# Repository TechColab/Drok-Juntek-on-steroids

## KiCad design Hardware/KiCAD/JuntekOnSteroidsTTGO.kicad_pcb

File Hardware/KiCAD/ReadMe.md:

# Goal:
-----
THT
No bigger than original board
Economise where possible
Include serial & other connector - just in case.

# SoFar:
------
## Gen.1 - on-board ADC
### 2021-03-17
Board outline is approx 80% of the original
All done first draft.
Options for connection to GNDA, GNDD or both.
Check size of TFT board when over-laid - perfect match for the minimalised outline.
### 2021-03-19
Swap GPIO12 & 15 for easier layout.
Put I2C on the port in place of SWIM as ESP32 doesn't have that.
Route !ON signal with jumpered options.
Move solder-bridges to bottom.
Add axis origin
Save schematic as PDF
### 2021-03-20
Confirm THT not SMT
Add TestPoint for flying-wire to Vin
Add solder bridge option for Vin_sense
Chane I2C pin order
### 2021-03-21
Renamed to correct spelling!
### 2021-05-03
Change pin numbering on I2C to match DFRobot pinout.
Re-route traces for I2C to ease changing to other pinouts.
Move Gerbers to sub-folder for neatness & easier handling.

## Gen.2 - dedicated ADC
### 2021-05-20
I2C connector as a 4-pin adjacent to a 2-pin.
Grove is 2mm not 2.54mm pitch but same pin-out as many others.
Along west edge to use horizontal pin headder, to make case / panel mount easier.
Test-point anchors for flying leads to off-board components.
In the schematic A0-A3 are on the ADC board & ADC0-ADC3 are on the TTGO - so they dont have conflicting names. 
### 2021-08-15
Major re-allocation of pins, noting multi-purpose functions of TTGO device (in only, boot restrictions etc.)
Route analogue signals via solder-bridge switch to both ADC1115 & TTGO to enable option of cheaper rough version.
Add pin for LoadPWM function so TTGO can connect the load by MOSFET and do controlled discharge of a battery.
Separate expansion connector into 2 separate rows for easier positioning & allow SIL only option.
Put external connections, including power, I2C, serial, DAC in a breadboard-friendly row.
Remove extra I2C, serial & power SIL headers as all can be accessed form the expansion SIL.
Set outline based on worst of DKP6012 & B3603, 1 col less on west, 1 row extra on north.
Add a spreadsheet table comparing pinouts of different PSUs & TTGO functions/restrictions.
### 2021-08-17
Remove unwanted resistor, rename a few resistors & two jumpers.
Add a jumper to break AltVinSense from J1.7 for models when CV/CC is on J1.3 & FanPWM is on J1.7
### 2021-08-19
Replace complex series of solder-bridge jumpers with a wire-patch-field.
Replace DIL expansion connector with SIL to free up board space & make easier for end-users.
Move TTGO south a bit for clearance with PSU cap.  Added a couple of caps on the 3.3V line.
Added a bit on north & west but still within consensus footprint.
Tweaked to avoid PSU capacitors on B3603.
### 2021-08-20
Replaced patch holes with 90-degree pin headers to allow use of common FM-FM jumper wires while avoiding TTGO overhang.
N.B. The horizontal pins closely interspace the solder side of the motherboard headder.
So I'd trim the excee from the motherboard headder first, then solder the patch headders while not fully pushed down.
Can also omit the patch headers and hard-wire.
### 2021-08-21
Initial routing and grounding done.
### 2021-08-22
Move small caps a bit. Drop LoadPWM from top left & add AltVinSense.
Remove a res & add one.
### 2021-08-24
Re-allocate R14 to series between ADC3 & J21.8
Change ADS1115 to be powered from 3.3V instead of 5V
Add 5V, GND, +3.3V on 12,13,14 of the extension connector J30
Labels for J30 etc.

# Need:
passive component values which match in both layout and schematic.
a pic directly above the proto board without the TTGO plugged in.
Clarification regarding 2-way solder bridge for "ADC1(AD5) / GPIO29(ESP)"

# WIP:

# ToDo:

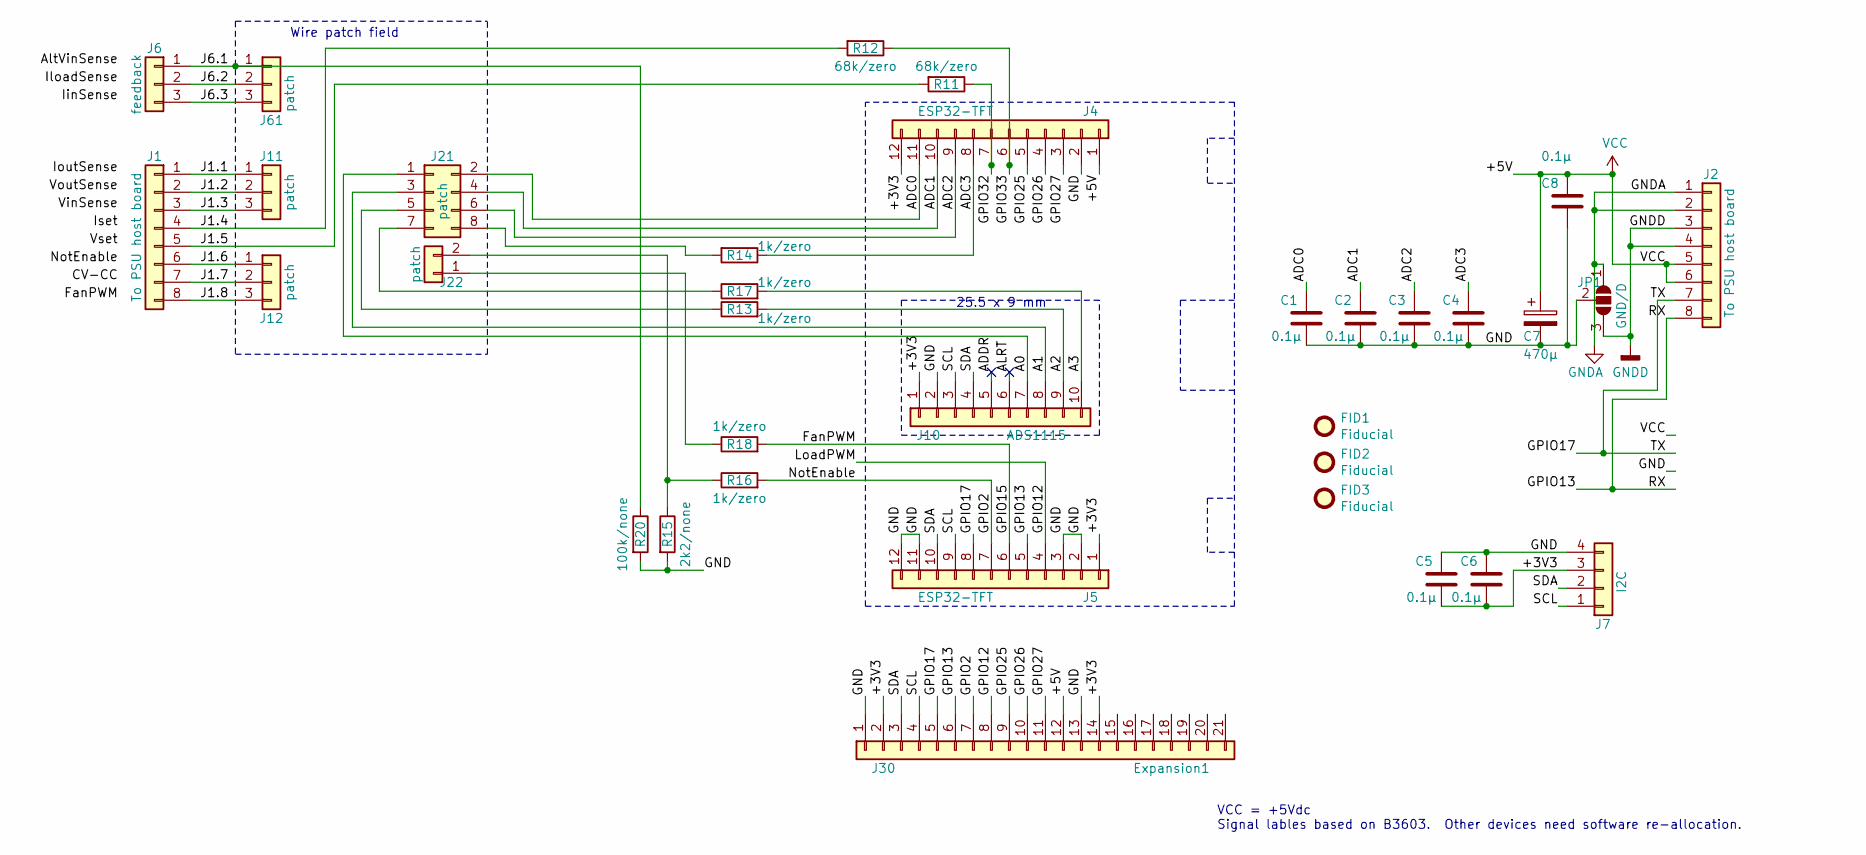
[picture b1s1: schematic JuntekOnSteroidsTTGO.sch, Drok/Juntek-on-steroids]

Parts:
C1, C2, C3, C4, C5, C6, C8: 0.1µ; C_Disc_D3.0mm_W1.6mm_P2.50mm
C7: 470µ; CP_Radial_D8.0mm_P3.50mm
FID1, FID2, FID3: Fiducial; Fiducial_0.5mm_Mask1mm
J1, J2: To PSU host board; PinHeader_1x08_P2.54mm_Vertical
J4, J5: ESP32-TFT; PinSocket_1x12_P2.54mm_Vertical
J6: feedback; PinHeader_1x03_P2.54mm_Horizontal
J7: I2C; JST_PH_B4B-PH-K_1x04_P2.00mm_Vertical
J10: ADS1115; PinSocket_1x10_P2.54mm_Vertical
J11, J12, J61: patch; PinHeader_1x03_P2.54mm_Horizontal
J21: patch; PinHeader_2x04_P2.54mm_Horizontal
J22: patch; PinHeader_1x02_P2.54mm_Horizontal
J30: Expansion1; PinHeader_1x21_P2.54mm_Horizontal
JP1: GND/D; SolderJumper-3_P1.3mm_Open_RoundedPad1.0x1.5mm
R11, R12: 68k/zero; R_Axial_DIN0204_L3.6mm_D1.6mm_P7.62mm_Horizontal
R13, R14, R16, R17, R18: 1k/zero; R_Axial_DIN0204_L3.6mm_D1.6mm_P7.62mm_Horizontal
R15: 2k2/none; R_Axial_DIN0204_L3.6mm_D1.6mm_P7.62mm_Horizontal
R20: 100k/none; R_Axial_DIN0204_L3.6mm_D1.6mm_P7.62mm_Horizontal

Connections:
/+3V3: C5.2, C6.2, J4.12, J5.1, J7.3, J10.1, J30.2, J30.14
/A0: J10.7, J21.1
/A1: J10.8, J21.3
/A2: J10.9, R13.2
/A3: J10.10, R17.2
/ADC0: C1.1, J4.11, J21.2
/ADC1: C2.1, J4.10, J21.4
/ADC2: C3.1, J4.9, J21.6
/ADC3: C4.1, J4.8, R14.1
/ADDR: J10.5
/ALRT: J10.6
/FanPWM: J5.6, R18.2
/GND: C1.2, C2.2, C3.2, C4.2, C5.1, C6.1, C7.2, C8.2, J4.2, J5.2, J5.3, J5.11, J5.12, J7.4, J10.2, J30.1, J30.13, JP1.2 (C), R15.2, R20.2
/GPIO2: J5.7, J30.7, R16.2
/GPIO12: J5.4, J30.8
/GPIO13: J2.8, J5.5, J30.6
/GPIO17: J2.7, J5.8, J30.5
/GPIO25: J4.5, J30.9
/GPIO26: J4.4, J30.10
/GPIO27: J4.3, J30.11
/GPIO32: J4.7, R11.1
/GPIO33: J4.6, R12.1
/J1.1: J1.1, J11.1
/J1.2: J1.2, J11.2
/J1.3: J1.3, J11.3
/J1.4: J1.4, R12.2
/J1.5: J1.5, R11.2
/J1.6: J1.6, J12.1
/J1.7: J1.7, J12.2
/J1.8: J1.8, J12.3
/J6.1: J6.1, J61.1, R20.1
/J6.2: J6.2, J61.2
/J6.3: J6.3, J61.3
/SCL: J5.9, J7.1, J10.3, J30.4
/SDA: J5.10, J7.2, J10.4, J30.3
GNDA: J2.1, J2.2, JP1.1 (A)
GNDD: J2.3, J2.4, JP1.3 (B)
unnamed: J21.5, R13.1
unnamed: J21.7, R17.1
unnamed: J21.8, R14.2
unnamed: J22.1, R18.1
unnamed: J22.2, R15.1, R16.1
VCC: C7.1, C8.1, J2.5, J2.6, J4.1, J30.12

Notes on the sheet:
VCC = +5Vdc Signal lables based on B3603. Other devices need software re-allocation.
25.5 x 9 mm
Wire patch field

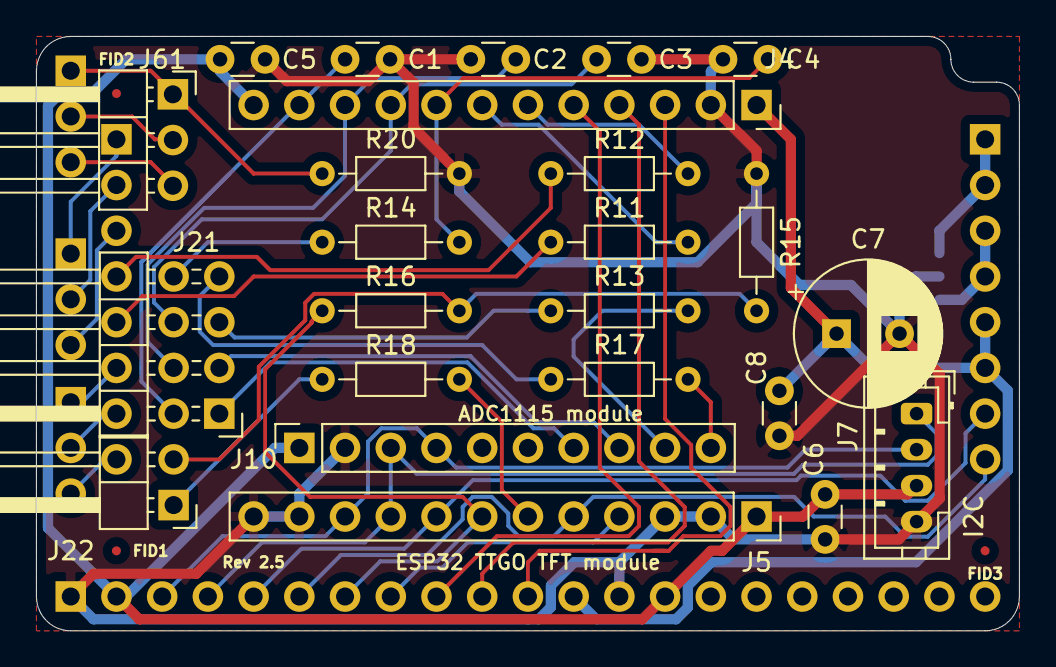
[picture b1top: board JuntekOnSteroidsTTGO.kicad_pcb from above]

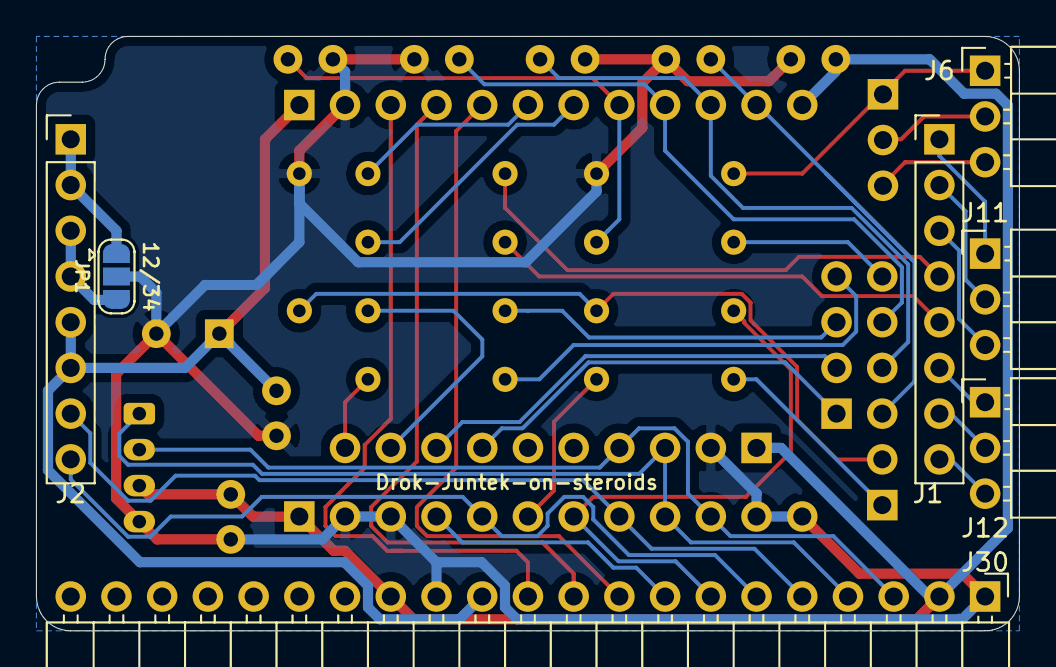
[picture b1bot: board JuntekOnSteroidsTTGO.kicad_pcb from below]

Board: 2 copper layers, 54.6 x 33.0 mm, 34 parts (7 on the bottom side), 41 nets.

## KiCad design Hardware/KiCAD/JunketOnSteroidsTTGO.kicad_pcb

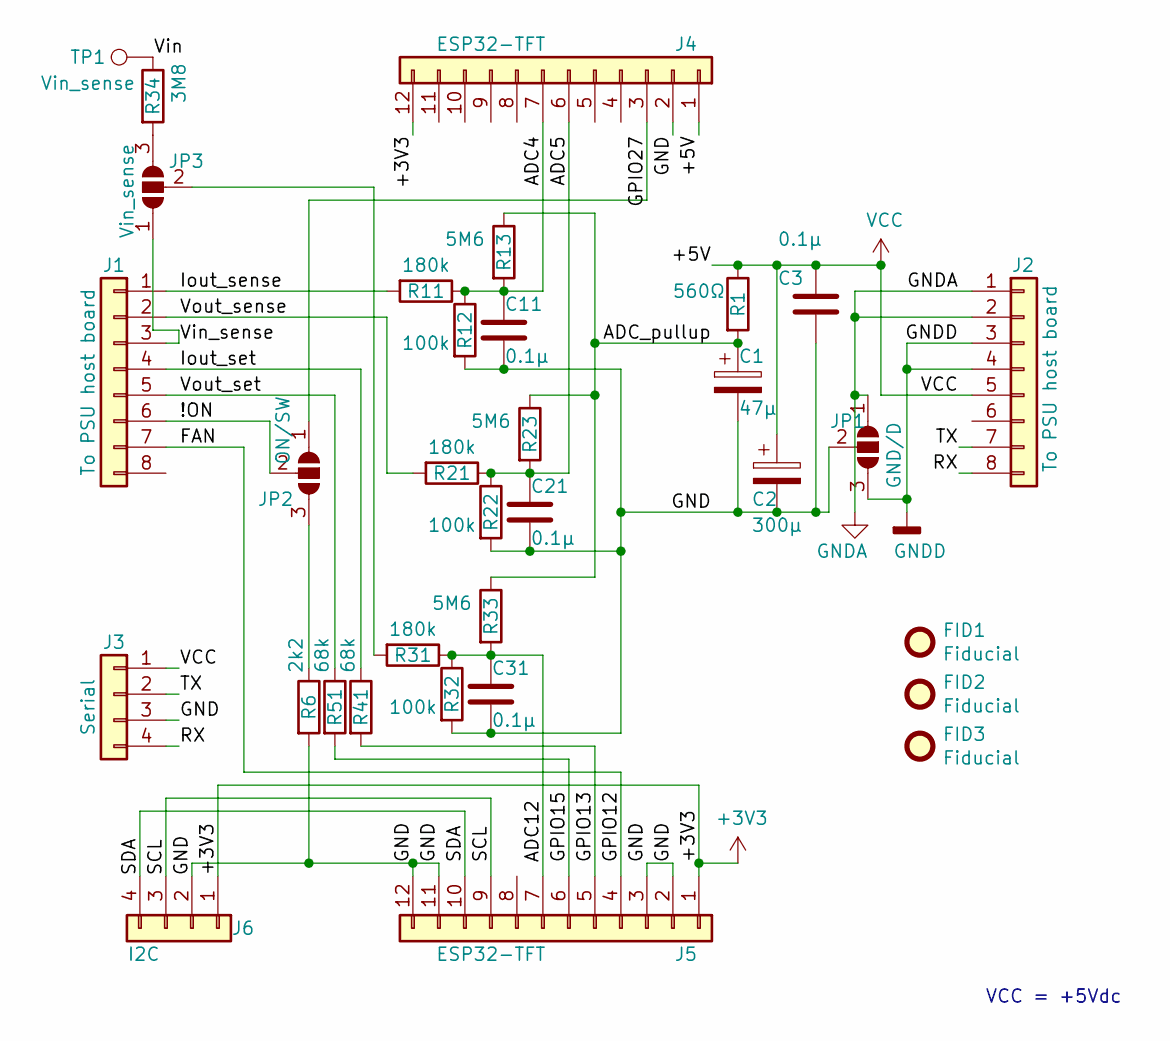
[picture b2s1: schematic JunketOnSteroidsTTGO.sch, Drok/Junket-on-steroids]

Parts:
C1: 47µ; CP_Radial_D5.0mm_P2.50mm
C2: 300µ; CP_Radial_D8.0mm_P2.50mm
C3, C11, C21, C31: 0.1µ; C_Disc_D4.7mm_W2.5mm_P5.00mm
FID1, FID2, FID3: Fiducial; Fiducial_0.5mm_Mask1mm
J1, J2: To PSU host board; PinHeader_1x08_P2.54mm_Vertical
J3: Serial; PinHeader_1x04_P2.54mm_Horizontal
J4, J5: ESP32-TFT; PinSocket_1x12_P2.54mm_Vertical
J6: I2C; PinHeader_1x04_P2.54mm_Horizontal
JP1: GND/D; SolderJumper-3_P1.3mm_Open_RoundedPad1.0x1.5mm
JP2: ON/SW; SolderJumper-3_P1.3mm_Open_RoundedPad1.0x1.5mm
JP3: Vin_sense; SolderJumper-3_P1.3mm_Open_RoundedPad1.0x1.5mm
R1: 560Ω; R_Axial_DIN0204_L3.6mm_D1.6mm_P7.62mm_Horizontal
R6: 2k2; R_Axial_DIN0204_L3.6mm_D1.6mm_P7.62mm_Horizontal
R11, R21, R31: 180k; R_Axial_DIN0204_L3.6mm_D1.6mm_P7.62mm_Horizontal
R12, R22, R32: 100k; R_Axial_DIN0204_L3.6mm_D1.6mm_P7.62mm_Horizontal
R13, R23, R33: 5M6; R_Axial_DIN0204_L3.6mm_D1.6mm_P7.62mm_Horizontal
R34: 3M8; R_Axial_DIN0204_L3.6mm_D1.6mm_P7.62mm_Horizontal
R41, R51: 68k; R_Axial_DIN0204_L3.6mm_D1.6mm_P7.62mm_Horizontal
TP1: Vin_sense; SolderWire-0.1sqmm_1x01_D0.4mm_OD1mm

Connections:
+3V3: J4.12, J5.1, J6.1
/!ON: J1.6, JP2.2 (C)
/ADC4: C11.1, J4.7, R11.1, R12.1, R13.2
/ADC5: C21.1, J4.6, R21.1, R22.1, R23.2
/ADC12: C31.1, J5.7, R31.1, R32.1, R33.2
/ADC_pullup: C1.1, R1.2, R13.1, R23.1, R33.1
/FAN: J1.7, J5.4
/GND: C1.2, C2.2, C3.2, C11.2, C21.2, C31.2, J3.3, J4.2, J5.2, J5.3, J5.11, J5.12, J6.2, JP1.2 (C), R6.2, R12.2, R22.2, R32.2
/GPIO13: J5.5, R41.2
/GPIO15: J5.6, R51.2
/GPIO27: J4.3, JP2.1 (A)
/Iout_sense: J1.1, R11.2
/Iout_set: J1.4, R41.1
/RX: J2.8, J3.4
/SCL: J5.9, J6.3
/SDA: J5.10, J6.4
/TX: J2.7, J3.2
/Vin: R34.1, TP1.1
/Vin_sense: J1.3, JP3.1 (A)
/Vout_sense: J1.2, R21.2
/Vout_set: J1.5, R51.1
GNDA: J2.1, J2.2, JP1.1 (A)
GNDD: J2.3, J2.4, JP1.3 (B)
unnamed: JP2.3 (B), R6.1
unnamed: JP3.2 (C), R31.2
unnamed: JP3.3 (B), R34.2
VCC: C2.1, C3.1, J2.5, J3.1, J4.1, R1.1

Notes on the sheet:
VCC = +5Vdc

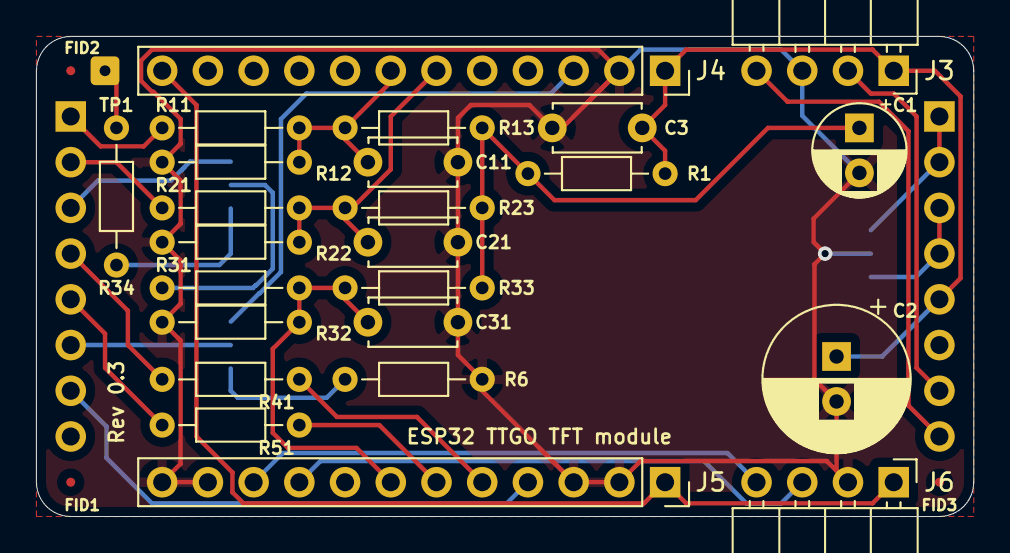
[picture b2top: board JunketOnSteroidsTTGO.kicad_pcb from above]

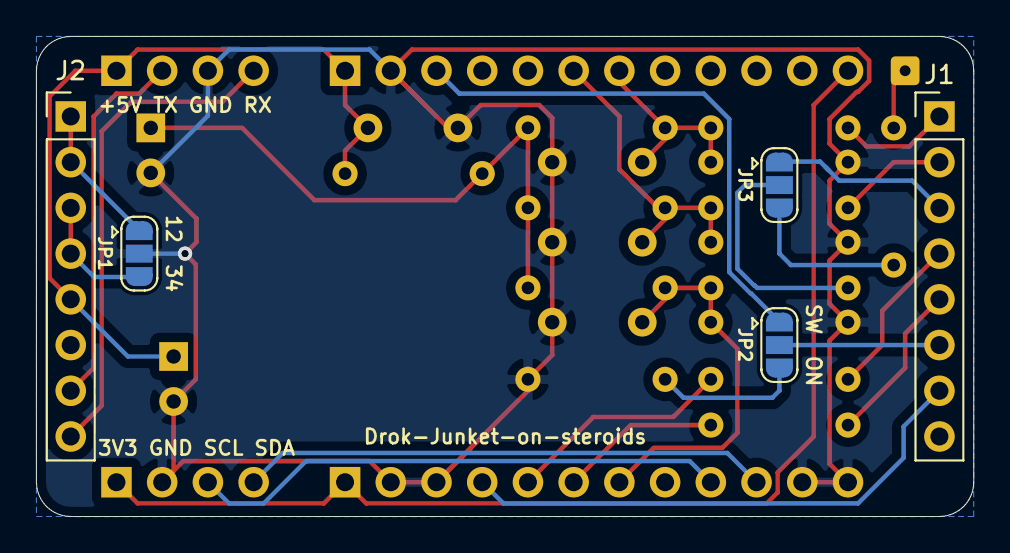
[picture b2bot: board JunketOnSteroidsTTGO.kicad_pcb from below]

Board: 2 copper layers, 52.1 x 26.7 mm, 33 parts (5 on the bottom side), 27 nets.

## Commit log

2021-03-18 First draft of THT PCB in KiCAD
2021-03-19 Swap GPIO12 & 15, Add !ON with solder-option, Replace SWIM with I2C
2021-03-20 Rev 0.3
2021-03-21 Rev 0.4
2021-03-21 Rev 0.4 with spelling correction
2021-05-03 Tidy I2C bits
2021-05-20 gen 2 initial draft
2021-05-20 increase dent
2021-05-22 Change exp. connector, add ADC caps
2021-08-15 v2.2
2021-08-15 v2.2 and a bit
2021-08-17 AltVinSense fix+
2021-08-19 wire-patch-config
2021-08-19 Avoid B3603 caps
2021-08-20 90-deg patch headers
2021-08-21 routed
2021-08-22 AltVinSense replacing LoadPWM
2021-08-24 Change ADS115 to 3.3V & other tweaks
2021-08-24 Update view from the west
